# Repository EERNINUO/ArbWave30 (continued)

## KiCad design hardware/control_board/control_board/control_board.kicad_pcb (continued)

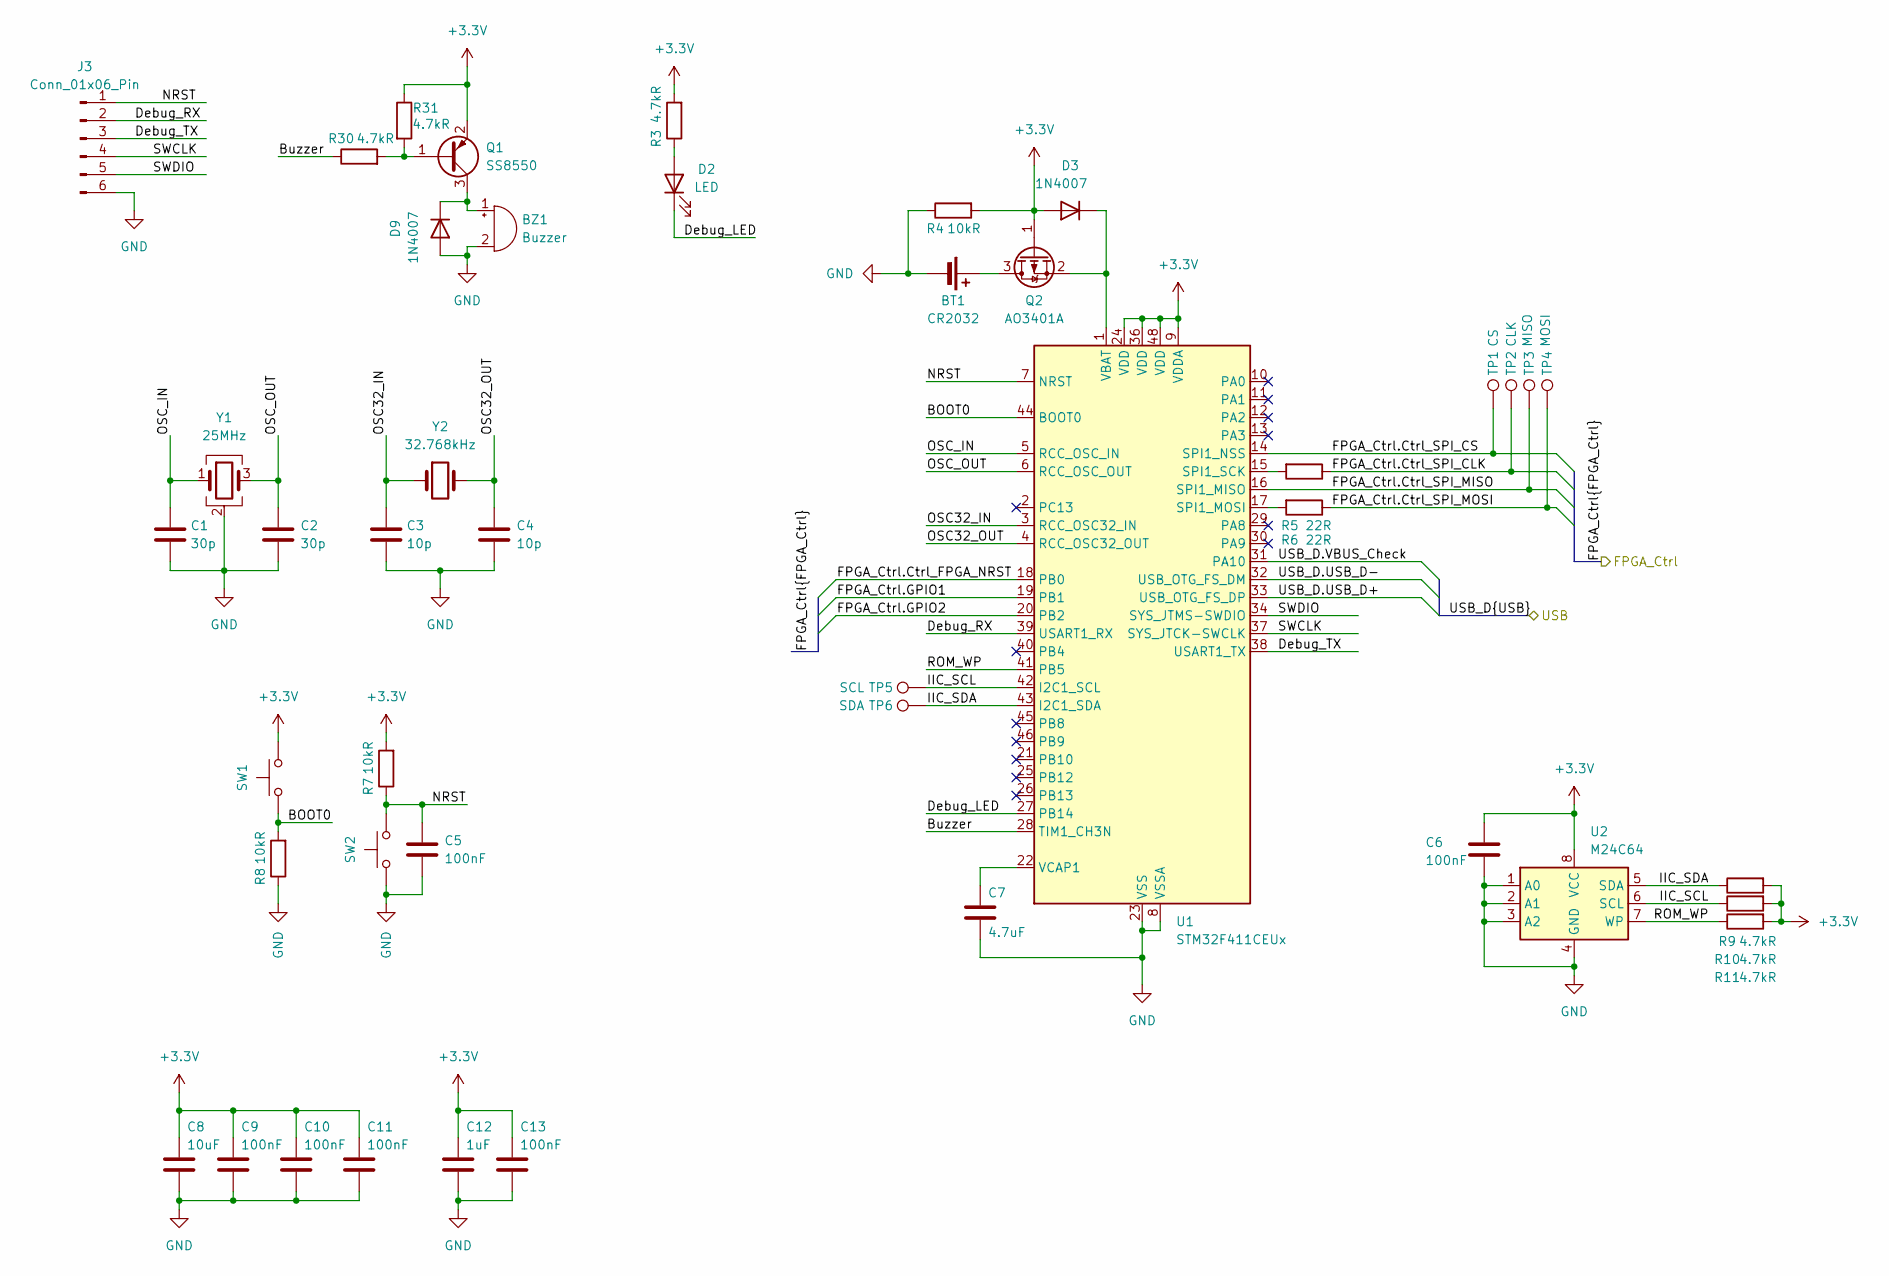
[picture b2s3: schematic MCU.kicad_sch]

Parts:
BT1: CR2032; BAT-TH_BS-05-A1BJ001
BZ1: Buzzer; MagneticBuzzer_StarMicronics_QMX
C1, C2: 30p; C_0603_1608Metric
C3, C4: 10p; C_0603_1608Metric
C5, C6, C9, C10, C11, C13: 100nF; C_0603_1608Metric
C7: 4.7uF; C_0603_1608Metric
C8: 10uF; C_0603_1608Metric
C12: 1uF; C_0603_1608Metric
D2: LED; LED_0603_1608Metric
D3, D9: 1N4007; D_SOD-123
J3: Conn_01x06_Pin; PinHeader_1x06_P2.54mm_Vertical
Q1: SS8550; SOT-23
Q2: AO3401A; SOT-23
R3, R9, R10, R11, R30, R31: 4.7kR; R_0603_1608Metric
R4, R7, R8: 10kR; R_0603_1608Metric
R5, R6: 22R; R_0402_1005Metric
SW1: BOOT0; SW_SPST_CK_RS282G05A3
SW2: NRST; SW_SPST_CK_RS282G05A3
TP1: CS; TestPoint_Pad_D1.0mm
TP2: CLK; TestPoint_Pad_D1.0mm
TP3: MISO; TestPoint_Pad_D1.0mm
TP4: MOSI; TestPoint_Pad_D1.0mm
TP5: SCL; TestPoint_Pad_D1.0mm
TP6: SDA; TestPoint_Pad_D1.0mm
U1: STM32F411CEUx; QFN-48-1EP_7x7mm_P0.5mm_EP5.6x5.6mm
U2: M24C64; SOIC-8_3.9x4.9mm_P1.27mm
Y1: 25MHz; Crystal_SMD_3225-4Pin_3.2x2.5mm
Y2: 32.768kHz; Crystal_SMD_3215-2Pin_3.2x1.5mm

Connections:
+3.3V: C6.1, C8.1, C9.1, C10.1, C11.1, C12.1, C13.1, D3.2 (A), Q1.2 (E), Q2.1 (G), R3.2, R4.2, R7.2, R9.2, R10.2, R11.2, R31.1, SW1.2 (B), U1.9 (VDDA), U1.24 (VDD), U1.36 (VDD), U1.48 (VDD), U2.8 (VCC); also elsewhere on the board
/FPGA_Ctrl.Ctrl_FPGA_NRST: U1.18 (PB0); also elsewhere on the board
/FPGA_Ctrl.Ctrl_SPI_CLK: R5.1, TP2.1 (1_1); also elsewhere on the board
/FPGA_Ctrl.Ctrl_SPI_CS: TP1.1 (1_1), U1.14 (SPI1_NSS); also elsewhere on the board
/FPGA_Ctrl.Ctrl_SPI_MISO: TP3.1 (1_1), U1.16 (SPI1_MISO); also elsewhere on the board
/FPGA_Ctrl.Ctrl_SPI_MOSI: R6.1, TP4.1 (1_1); also elsewhere on the board
/FPGA_Ctrl.GPIO1: U1.19 (PB1); also elsewhere on the board
/FPGA_Ctrl.GPIO2: U1.20 (PB2); also elsewhere on the board
/MCU/BOOT0: R8.2, SW1.1 (A), U1.44 (BOOT0)
/MCU/Buzzer: R30.1, U1.28 (TIM1_CH3N)
/MCU/Debug_LED: D2.1 (K), U1.27 (PB14)
/MCU/Debug_RX: J3.2, U1.39 (USART1_RX)
/MCU/Debug_TX: J3.3, U1.38 (USART1_TX)
/MCU/IIC_SCL: R10.1, TP5.1 (1_1), U1.42 (I2C1_SCL), U2.6 (SCL)
/MCU/IIC_SDA: R9.1, TP6.1 (1_1), U1.43 (I2C1_SDA), U2.5 (SDA)
/MCU/NRST: C5.1, J3.1, R7.1, SW2.2 (B), U1.7 (NRST)
/MCU/OSC32_IN: C3.1, U1.3 (RCC_OSC32_IN), Y2.1
/MCU/OSC32_OUT: C4.1, U1.4 (RCC_OSC32_OUT), Y2.2
/MCU/OSC_IN: C1.1, U1.5 (RCC_OSC_IN), Y1.1
/MCU/OSC_OUT: C2.1, U1.6 (RCC_OSC_OUT), Y1.3
/MCU/ROM_WP: R11.1, U1.41 (PB5), U2.7 (WP)
/MCU/SWCLK: J3.4, U1.37 (SYS_JTCK-SWCLK)
/MCU/SWDIO: J3.5, U1.34 (SYS_JTMS-SWDIO)
/USB_D.USB_D+: U1.33 (USB_OTG_FS_DP); also elsewhere on the board
/USB_D.USB_D-: U1.32 (USB_OTG_FS_DM); also elsewhere on the board
/USB_D.VBUS_Check: U1.31 (PA10); also elsewhere on the board
GND: BT1.2 (-), BZ1.2 (-), C1.2, C2.2, C3.2, C4.2, C5.2, C6.2, C7.1, C8.2, C9.2, C10.2, C11.2, C12.2, C13.2, D9.2 (A), J3.6, R4.1, R8.1, SW2.1 (A), U1.8 (VSSA), U1.23 (VSS), U1.35 (VSS), U1.47 (VSS), U1.49 (VSS), U2.1 (A0), U2.2 (A1), U2.3 (A2), U2.4 (GND), Y1.2 (G), Y1.4 (G); also elsewhere on the board
unnamed: BT1.1 (+), Q2.3 (D)
unnamed: BZ1.1 (+), D9.1 (K), Q1.3 (C)
unnamed: D2.2 (A), R3.1
unnamed: D3.1 (K), Q2.2 (S), U1.1 (VBAT)
unnamed: Q1.1 (B), R30.2, R31.2
unnamed: R5.2, U1.15 (SPI1_SCK)
unnamed: R6.2, U1.17 (SPI1_MOSI)
unnamed: C7.2, U1.22 (VCAP1)

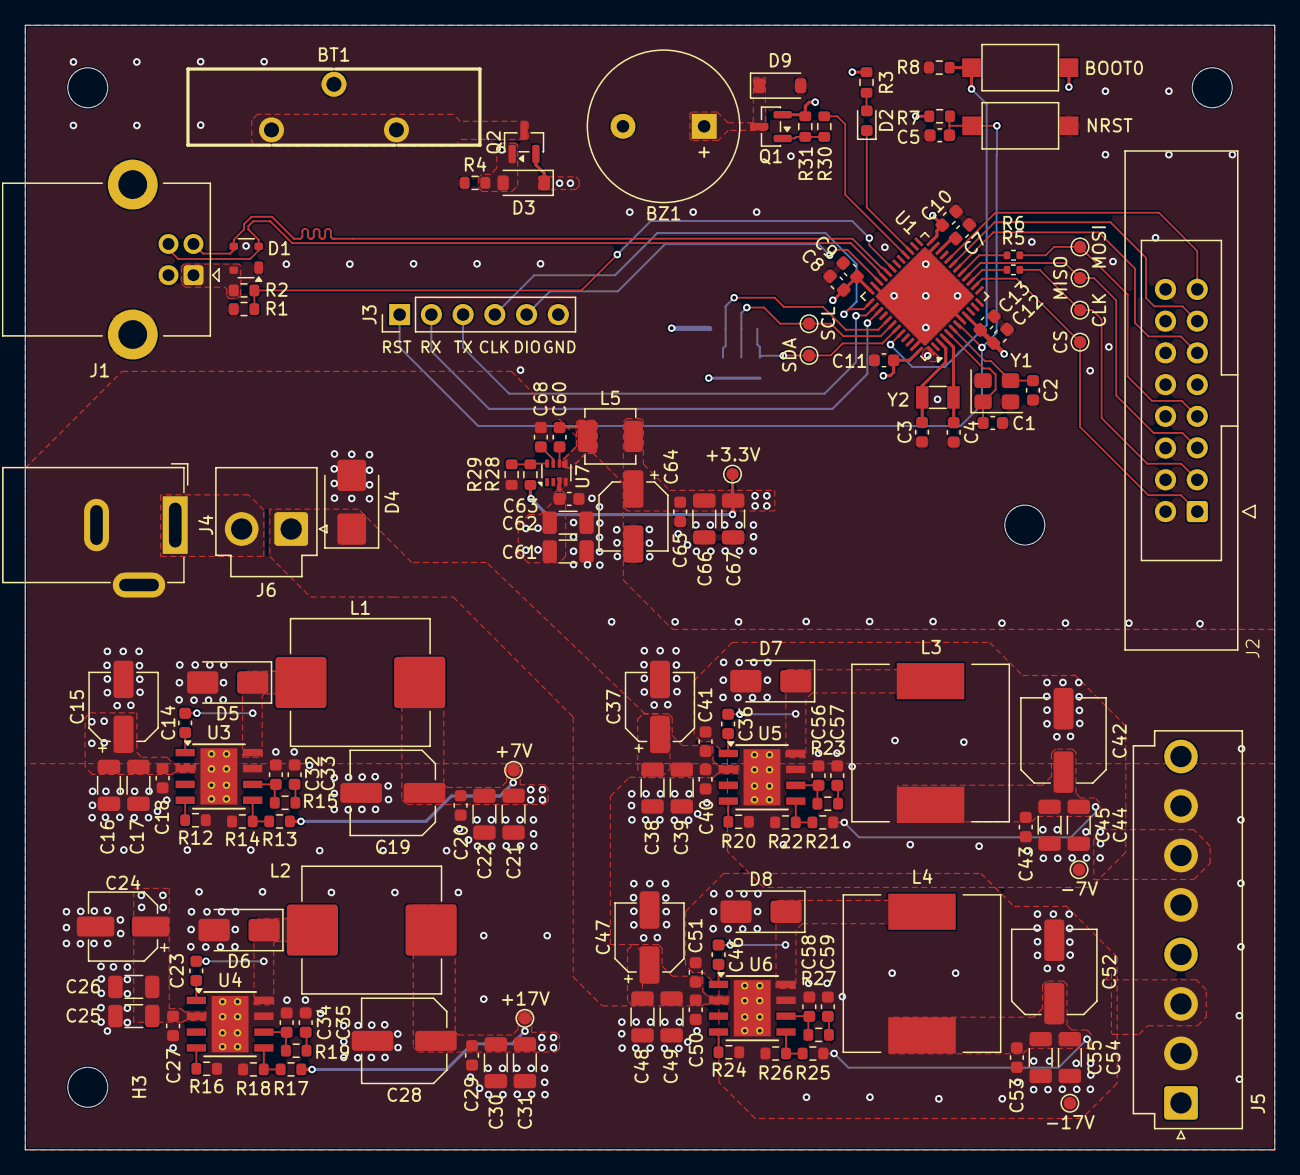
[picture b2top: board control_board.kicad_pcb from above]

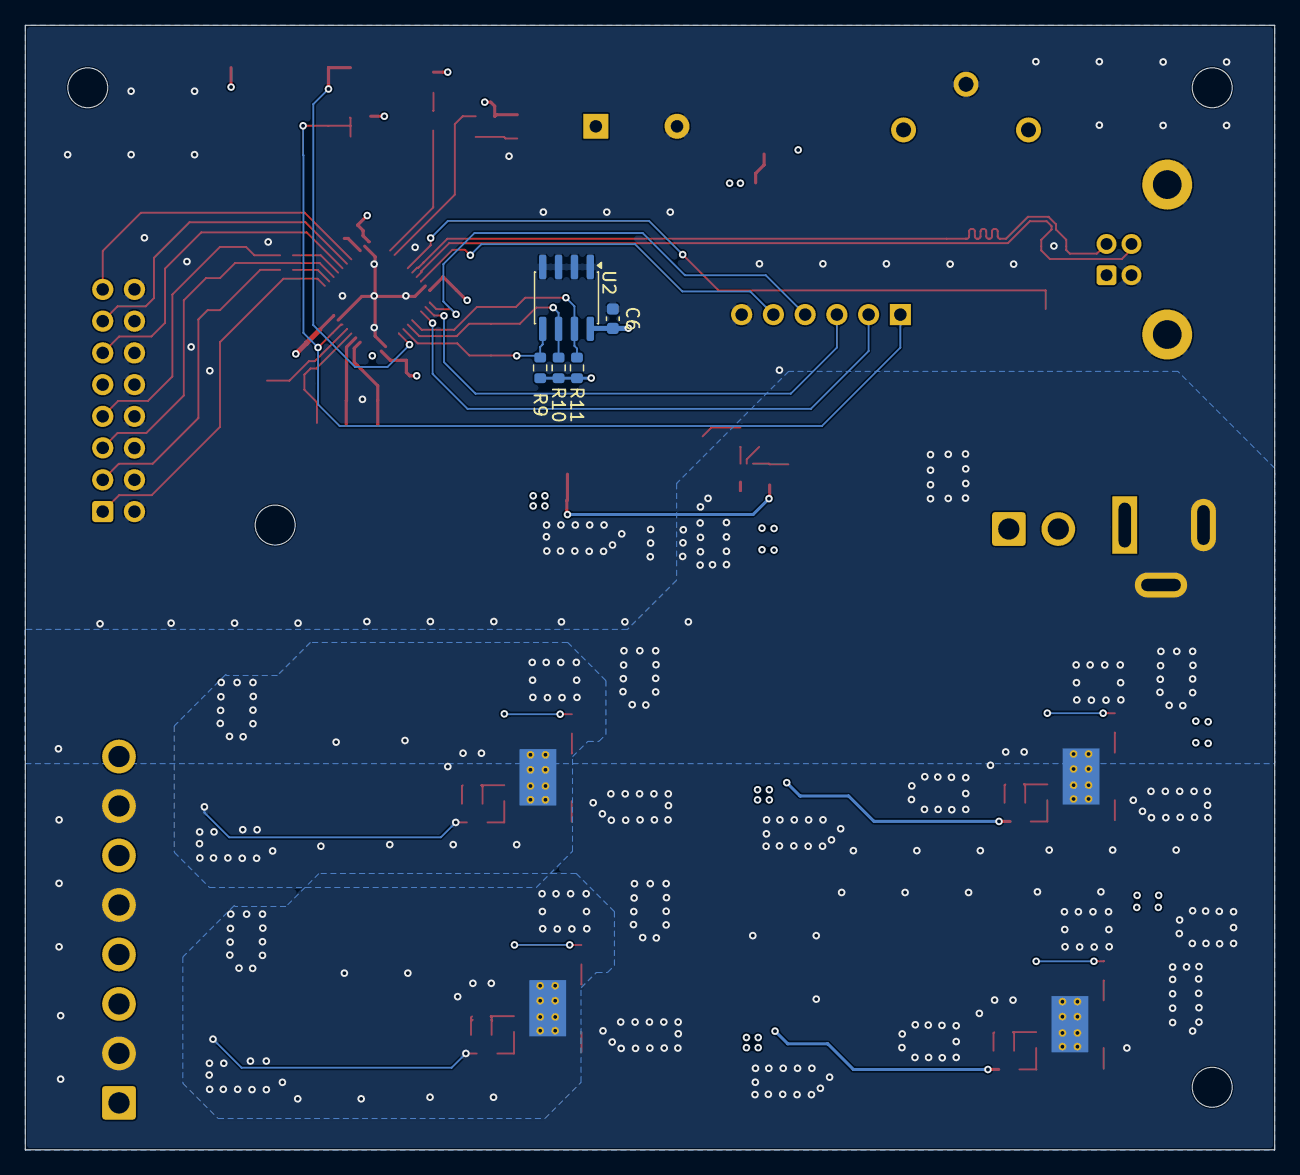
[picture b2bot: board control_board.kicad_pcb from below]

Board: 4 copper layers, 100.0 x 90.0 mm, 149 parts (5 on the bottom side), 70 nets.

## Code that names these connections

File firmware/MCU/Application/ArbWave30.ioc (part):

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Mcu.Name=STM32F411C(C-E)Ux
Mcu.Package=UFQFPN48
Mcu.UserName=STM32F411CEUx
PA10.GPIOParameters=GPIO_Label,GPIO_ModeDefaultEXTI
PA10.GPIO_Label=VBUS_Check
PA10.GPIO_ModeDefaultEXTI=GPIO_MODE_IT_RISING_FALLING
PA10.Signal=GPXTI10
PA11.Mode=Device_Only
PA11.Signal=USB_OTG_FS_DM
PA12.Mode=Device_Only
PA12.Signal=USB_OTG_FS_DP
PA13.Mode=Serial_Wire
PA13.Signal=SYS_JTMS-SWDIO
PA14.Mode=Serial_Wire
PA14.Signal=SYS_JTCK-SWCLK
PA15.Mode=Asynchronous
PA15.Signal=USART1_TX
PA4.GPIOParameters=GPIO_Speed,PinState,GPIO_Label
PA4.GPIO_Label=SPI1_CS
PA4.GPIO_Speed=GPIO_SPEED_FREQ_VERY_HIGH
PA4.PinState=GPIO_PIN_SET
PA4.Signal=GPIO_Output
PA5.Mode=Full_Duplex_Master
PA5.Signal=SPI1_SCK
PA6.Mode=Full_Duplex_Master
PA6.Signal=SPI1_MISO
PA7.Mode=Full_Duplex_Master
PA7.Signal=SPI1_MOSI
PB0.GPIOParameters=GPIO_Speed,PinState,GPIO_Label
PB0.GPIO_Label=FPGA_NRST
PB0.GPIO_Speed=GPIO_SPEED_FREQ_HIGH
PB0.PinState=GPIO_PIN_SET
PB0.Signal=GPIO_Output
PB1.GPIOParameters=GPIO_Label
PB1.GPIO_Label=FPGA_INT
PB1.Signal=GPXTI1
PB14.GPIOParameters=GPIO_Label
PB14.GPIO_Label=Debug_LED
PB14.Signal=GPIO_Output
PB15.GPIOParameters=GPIO_Label
PB15.GPIO_Label=Buzzer
PB15.Mode=PWM Generation3 CH3N
PB15.Signal=TIM1_CH3N
PB2.GPIOParameters=GPIO_Speed,PinState,GPIO_Label
PB2.GPIO_Label=GPIO2
PB2.GPIO_Speed=GPIO_SPEED_FREQ_VERY_HIGH
PB2.PinState=GPIO_PIN_RESET
PB2.Signal=GPIO_Output
PB3.Mode=Asynchronous
PB3.Signal=USART1_RX
PB5.GPIOParameters=GPIO_Speed,GPIO_Label
PB5.GPIO_Label=ROM_WP
PB5.GPIO_Speed=GPIO_SPEED_FREQ_LOW
PB5.Signal=GPIO_Output
PB6.Mode=I2C
PB6.Signal=I2C1_SCL
PB7.Mode=I2C
PB7.Signal=I2C1_SDA
PC14-OSC32_IN.Mode=LSE-External-Oscillator
PC14-OSC32_IN.Signal=RCC_OSC32_IN
PC15-OSC32_OUT.Mode=LSE-External-Oscillator
PC15-OSC32_OUT.Signal=RCC_OSC32_OUT
PH0\ -\ OSC_IN.Mode=HSE-External-Oscillator
PH0\ -\ OSC_IN.Signal=RCC_OSC_IN
PH1\ -\ OSC_OUT.Mode=HSE-External-Oscillator
PH1\ -\ OSC_OUT.Signal=RCC_OSC_OUT
RCC.HSE_VALUE=25000000
RCC.SYSCLKFreq_VALUE=96000000
RCC.SYSCLKSource=RCC_SYSCLKSOURCE_PLLCLK
board=custom

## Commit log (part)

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2026-04-04 添加 .gitignore 文件和更新 README.md
2026-04-04 添加 30M 任意波形发生器技术规格书文档
2026-04-06 技术规格书初始架构；更改电源要求；添加部分数据手册
2026-04-07 FPGA选型决策
2026-04-11 添加一些 LICENSE
2026-04-20 1、简化系统框图 2、完善模拟前端架构 3、确定了一些器件的选型
2026-04-22 1、添加时钟设计 2、添加AI辅助声明
2026-04-25 MCU最小系统设计
2026-04-25 MCU<->FPGA通信协议初步设计
2026-04-25 移除总览错误放置的模块
2026-04-27 v1.0/v2.0 放弃本地控制决策记录 Assisted-by: DeepSeek
2026-04-29 修改DAC选型 Assisted-by: DeepSeek - 文档框架
2026-04-30 绘制原理图符号库
2026-04-30 修改DAC选型
2026-05-01 调整文档格式
2026-05-01 完成FPGA与DAC接口
2026-05-02 自动化工作流-README.md动态渲染
2026-05-02 docs: auto-render README from template [skip-ci]
2026-05-03 电源轨功耗计算
2026-05-04 完成DAC电路设计
2026-05-05 修改电源设计
2026-05-06 补充模拟板电源设计细节
2026-05-06 1、FPGA最小系统原理图 2、DAC电路原理图 3、FPGA DAC 预布局
2026-05-07 模拟板文档添加 FPGA DAC 原理图截图
2026-05-09 1、添加滤波器设计笔记 2、完成重构滤波器设计
2026-05-09 滤波器仿真
2026-05-09 滤波器拓扑结构选型
2026-05-11 完成差分转单端电路设计
2026-05-12 simulink: 模拟前端-差分转单端仿真
2026-05-12 feat: 滤波器&差分转单端电路原理图
2026-05-13 feat：时钟电路原理图
2026-05-13 docs：时钟电路设计
2026-05-13 feat：完成模拟板板间接口设计
2026-05-13 debug：修正 反向DC-DC匹配网络元件值；修正板间接口文档电源连接器定义
2026-05-14 docs:：修正公式显示问题；调整图片格式
2026-05-14 docs：控制板电源设计
2026-05-15 feat：模拟板电源 原理图设计
2026-05-15 fixbug：修复 1.0V DCDC错误；根据PCB布局修改DCDC输入/输出电解电容参数
2026-05-15 feat：重构滤波器预布局
2026-05-15 feat：原理图添加测试点
2026-05-15 docs：修改测试点位置
2026-05-15 feat：差分转单端预布局
2026-05-15 feat：共模反馈电路预布局
2026-05-15 feat：时钟电路预布局
2026-05-16 feat：模拟板电源预布局
2026-05-17 feat：FPGA-DAC接口布线
2026-05-17 feat：FPGA布线
2026-05-17 feat：DAC布线
2026-05-17 docs：完成PCB布局布线指南
2026-05-17 feat：时钟电路布线
2026-05-18 feat：重构滤波器布局，共模反馈布局
2026-05-18 feat：差分转单端电路布线
2026-05-18 feat：电源布线完成
2026-05-18 feat：根据PCB微调原理图
2026-05-21 feat：添加缝合过孔
2026-05-22 feat：添加平衡铜
2026-05-23 docs：MCU最小系统原理图
2026-05-23 feat：MCU最小系统，USB接口原理图
2026-05-23 docs：USB接口、EEPROM原理图
2026-05-23 feat：EEPROM原理图
2026-05-24 docs：调整 ADR-002 描述
2026-05-24 docs：根据引脚位置修改调试接口线序
2026-05-26 feat：控制板电源原理图
2026-05-26 feat：±7V电源移动到控制板（原理图修改）
2026-05-27 feat：MCU最小系统预布局
2026-05-27 debug：蜂鸣器驱动电路；debug LED；电源输出排针
2026-05-27 feat：调试接口预布局；USB接口预布局
2026-05-27 feat：电源预布局
2026-05-27 feat：整版布局
2026-05-27 feat：MCU、USB、EEPROM、Debug布线
2026-05-27 feat：电源布线
2026-05-31 feat：DCDC移至控制板
2026-05-31 debug：输出10MHz时钟线宽修正为5.96mm(50Ω)
2026-05-31 feat：导出模拟板 BOM
2026-06-06 docs：±7V DC-DC 移至控制板
2026-06-06 license：修改版权声明
2026-06-06 docs：修改项目状态
2026-06-14 feat：创建工程
2026-06-15 feat：定义顶部接口
2026-06-15 feat：生成时钟发生器寄存器值
2026-06-16 docs：更新文档状态
2026-06-16 docs：模拟板MVP软件框图
2026-06-18 docs：添加 SCPI-1999 技术规范文档
2026-06-18 docs：完善软件设计文档概述部分
2026-06-19 docs：修正文档编号
2026-06-20 docs：将板间通信方式从命令式改为寄存器映射式
2026-06-21 feat：模拟板 MVP 配置通过
2026-06-21 docs:：规定通信协议内容
2026-06-22 docs：定义寄存器映射总表
2026-06-22 feat：创建MCU工程
2026-06-23 feat：MCU最小系统测试程序
2026-06-24 feat：FPGA最小系统测试程序
2026-06-27 feat：FPGA_Clock_test Project
2026-06-28 feat：完成时钟生成、系统控制模块
2026-06-29 feat：DCO域异步复位同步释放
2026-06-29 feat：添加波形生成模块，实例化DDS II IP核；修正系统时钟频率参数
